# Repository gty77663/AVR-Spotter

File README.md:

# AVR Spotter
  
[Credit for logo inspiration](https://commons.m.wikimedia.org/wiki/File:Spark_By_Alexander_Skowalsky_756341.svg)

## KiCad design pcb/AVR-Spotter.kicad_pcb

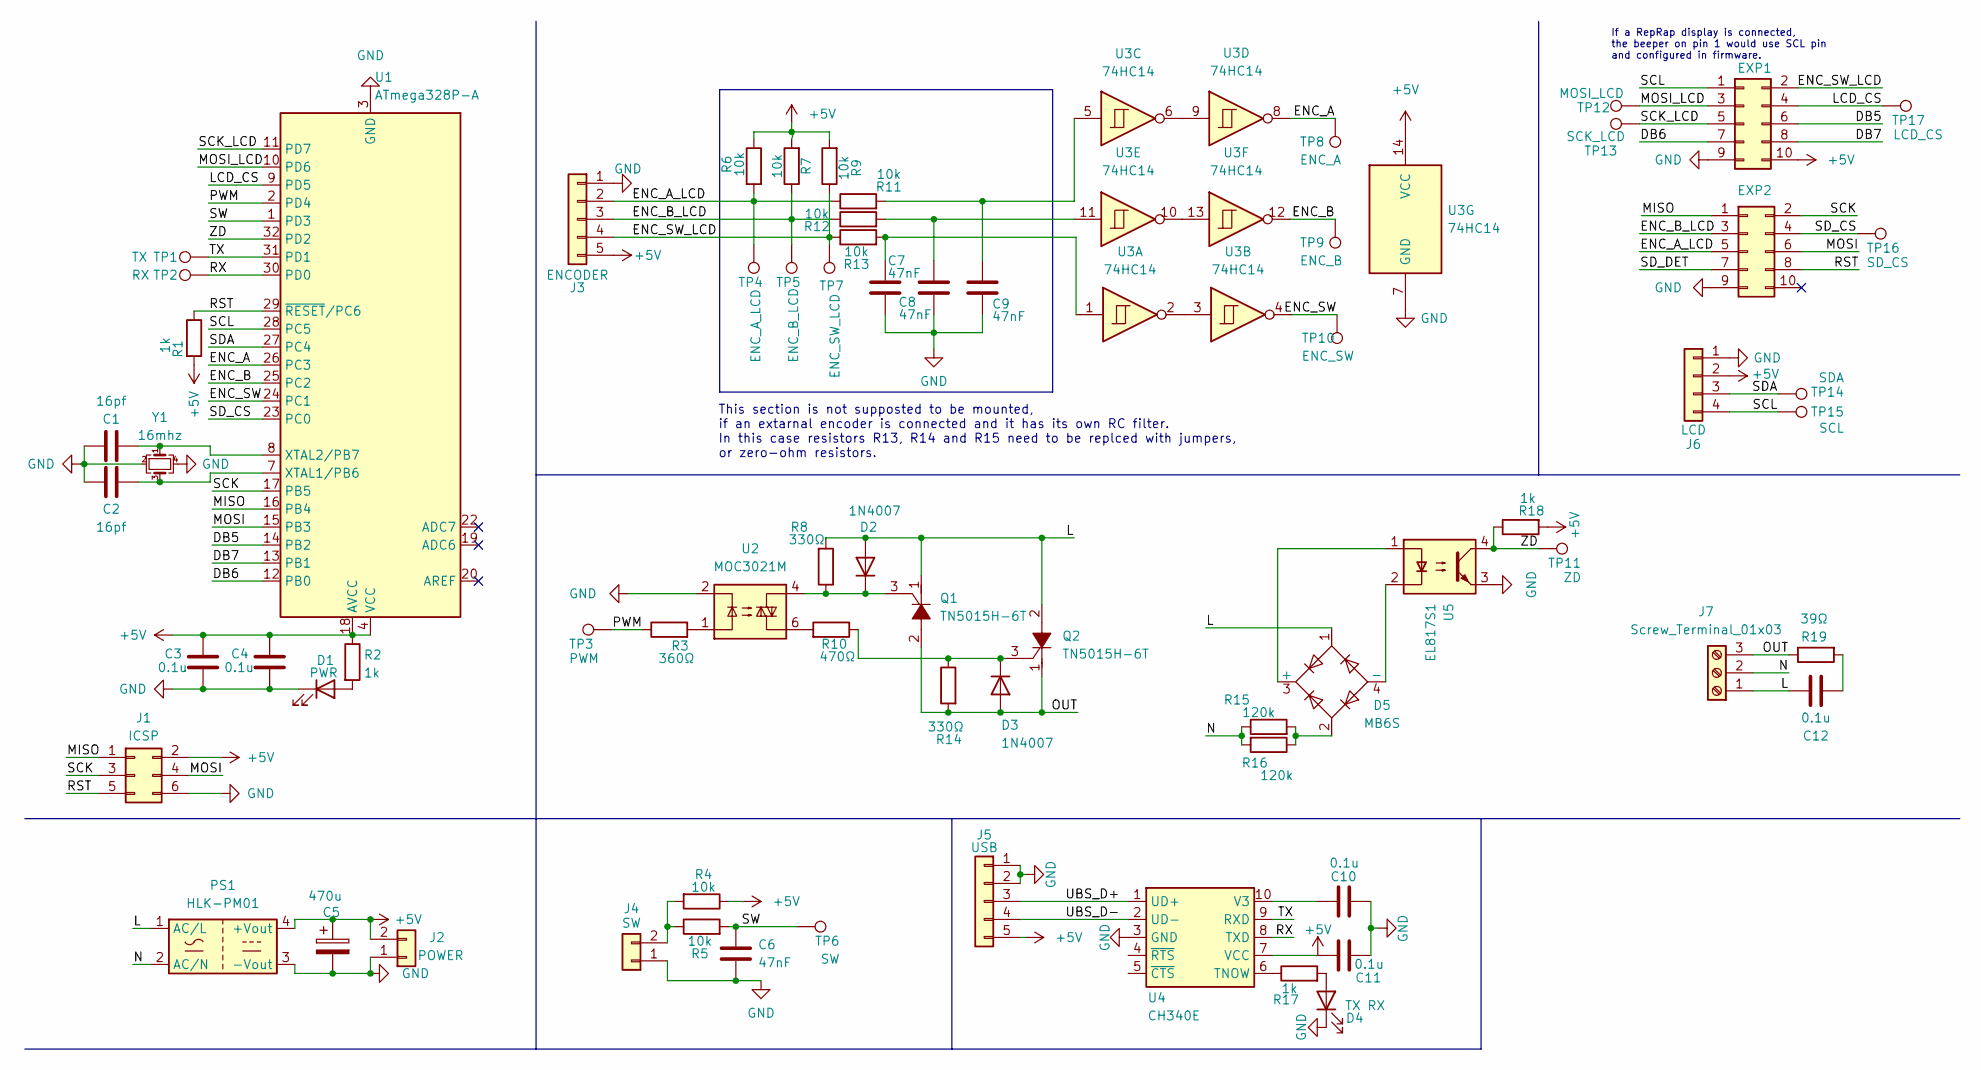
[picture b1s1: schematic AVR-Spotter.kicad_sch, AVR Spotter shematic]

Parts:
C1, C2: 16pf; C_0402_1005Metric
C3, C4, C10, C11: 0.1u; C_0402_1005Metric
C5: 470u; CP_Radial_D6.3mm_P2.50mm
C6, C7, C8, C9: 47nF; C_0402_1005Metric
C12: 0.1u; C_1206_3216Metric
D1: PWR; LED_0603_1608Metric
D2: 1N4007; D_SMA
D3: 1N4007; D_SMA; LCSC Part C727081
D4: TX RX; LED_0603_1608Metric
D5: MB6S; TO-269AA
EXP1, EXP2: Header_2x05_P2.54mm_Vertical; IDC-Header_2x05_P2.54mm_Vertical
J1: ICSP; PinHeader_2x03_P2.54mm_Vertical
J2: POWER; JST_XH_B2B-XH-A_1x02_P2.50mm_Vertical
J3: ENCODER; JST_XH_B5B-XH-A_1x05_P2.50mm_Vertical
J4: SW; JST_XH_B2B-XH-A_1x02_P2.50mm_Vertical
J5: USB; PinHeader_1x05_P2.54mm_Vertical
J6: LCD; JST_XH_B4B-XH-A_1x04_P2.50mm_Vertical
J7: Screw_Terminal_01x03; PhoenixContact_GMSTBA_2,5_3-G-7,62_1x03_P7.62mm_Horizontal
PS1: HLK-PM01; Converter_ACDC_HiLink_HLK-PMxx
Q1, Q2: TN5015H-6T; TO-220-3; MPN TN5015H-6T; Digi-Key_PN 497-17607-ND
R1, R2, R17, R18: 1k; R_0402_1005Metric
R3: 360Ω; R_0402_1005Metric
R4, R5, R6, R7, R9, R11, R12, R13: 10k; R_0402_1005Metric
R8, R14: 330Ω; R_1206_3216Metric_Pad1.30x1.75mm_HandSolder; LCSC Part C25374
R10: 470Ω; R_1210_3225Metric_Pad1.30x2.65mm_HandSolder; LCSC Part C473642
R15, R16: 120k; R_1210_3225Metric_Pad1.30x2.65mm_HandSolder
R19: 39Ω; R_1210_3225Metric
TP1: TX; TestPoint_Pad_D1.0mm
TP2: RX; TestPoint_Pad_D1.0mm
TP3: PWM; TestPoint_Pad_D1.0mm
TP4: ENC_A_LCD; TestPoint_Pad_D1.0mm
TP5: ENC_B_LCD; TestPoint_Pad_D1.0mm
TP6: SW; TestPoint_Pad_D1.0mm
TP7: ENC_SW_LCD; TestPoint_Pad_D1.0mm
TP8: ENC_A; TestPoint_Pad_D1.0mm
TP9: ENC_B; TestPoint_Pad_D1.0mm
TP10: ENC_SW; TestPoint_Pad_D1.0mm
TP11: ZD; TestPoint_Pad_D1.0mm
TP12: MOSI_LCD; TestPoint_Pad_D1.0mm
TP13: SCK_LCD; TestPoint_Pad_D1.0mm
TP14: SDA; TestPoint_Pad_D1.0mm
TP15: SCL; TestPoint_Pad_D1.0mm
TP16: SD_CS; TestPoint_Pad_D1.0mm
TP17: LCD_CS; TestPoint_Pad_D1.0mm
U1: ATmega328P-A; TQFP-32_7x7mm_P0.8mm
U2: MOC3021M; SMDIP-6_W9.53mm
U3: 74HC14; SO-14_3.9x8.65mm_P1.27mm
U4: CH340E; MSOP-10_3x3mm_P0.5mm
U5: EL817S1; SMD-4_4.6x6.5mm_P2.54mm
Y1: 16mhz; Crystal_SMD_3225-4Pin_3.2x2.5mm

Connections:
+5V: C3.1, C4.1, C5.1, EXP1.10, J1.2, J2.2, J3.5, J5.5, J6.2, PS1.4 (+Vout), R1.2, R2.1, R4.1, R6.1, R7.2, R9.2, R18.2, U1.4 (VCC), U1.6 (VCC), U1.18 (AVCC), U3.14 (VCC)
/DB5: EXP1.6, U1.14 (PB2)
/DB6: EXP1.7, U1.12 (PB0)
/DB7: EXP1.8, U1.13 (PB1)
/ENC_A: TP8.1, U1.26 (PC3), U3.8
/ENC_A_LCD: EXP2.5, J3.2, R6.2, R11.1, TP4.1
/ENC_B: TP9.1, U1.25 (PC2), U3.12
/ENC_B_LCD: EXP2.3, J3.3, R7.1, R12.1, TP5.1
/ENC_SW: TP10.1, U1.24 (PC1), U3.4
/ENC_SW_LCD: EXP1.2, J3.4, R9.1, R13.1, TP7.1
/L: C12.2, D2.2 (A), D5.1, J7.1, PS1.1 (AC/L), Q1.1 (C), Q2.2 (A), R8.2
/LCD_CS: EXP1.4, TP17.1, U1.9 (PD5)
/MISO: EXP2.1, J1.1, U1.16 (PB4)
/MOSI: EXP2.6, J1.4, U1.15 (PB3)
/MOSI_LCD: EXP1.3, TP12.1, U1.10 (PD6)
/N: J7.2, PS1.2 (AC/N), R15.1, R16.2
/OUT: D3.2 (A), J7.3, Q1.2 (A), Q2.1 (C), R14.2, R19.1
/PWM: R3.1, TP3.1, U1.2 (PD4)
/RST: EXP2.8, J1.5, R1.1, U1.29 (~RESET/PC6)
/RX: TP2.1, U1.30 (PD0), U4.8 (TXD)
/SCK: EXP2.2, J1.3, U1.17 (PB5)
/SCK_LCD: EXP1.5, TP13.1, U1.11 (PD7)
/SCL: EXP1.1, J6.4, TP15.1, U1.28 (PC5)
/SDA: J6.3, TP14.1, U1.27 (PC4)
/SD_CS: EXP2.4, TP16.1, U1.23 (PC0)
/SD_DET: EXP2.7
/SW: C6.1, R5.2, TP6.1, U1.1 (PD3)
/TX: TP1.1, U1.31 (PD1), U4.9 (RXD)
/UBS_D+: J5.3, U4.1 (UD+)
/UBS_D-: J5.4, U4.2 (UD-)
/ZD: R18.1, TP11.1, U1.32 (PD2), U5.4
GND: C1.2, C2.1, C3.2, C4.2, C5.2, C6.2, C7.2, C8.2, C9.2, C10.1, C11.1, D1.1 (K), D4.1 (K), EXP1.9, EXP2.9, J1.6, J2.1, J3.1, J4.1, J5.1, J5.2, J6.1, PS1.3 (-Vout), U1.3 (GND), U1.5 (GND), U1.21 (GND), U2.2, U3.7 (GND), U4.3 (GND), U5.3, Y1.2, Y1.4
unnamed: C1.1, U1.8 (XTAL2/PB7), Y1.1
unnamed: C2.2, U1.7 (XTAL1/PB6), Y1.3
unnamed: C7.1, R13.2, U3.1
unnamed: C8.1, R12.2, U3.11
unnamed: C9.1, R11.2, U3.5
unnamed: C10.2, U4.10 (V3)
unnamed: C11.2, U4.7 (VCC)
unnamed: C12.1, R19.2
unnamed: D1.2 (A), R2.2
unnamed: D2.1 (K), Q1.3 (G), R8.1, U2.4
unnamed: D3.1 (K), Q2.3 (G), R10.1, R14.1
unnamed: D4.2 (A), R17.2
unnamed: D5.2, R15.2, R16.1
unnamed: D5.3 (+), U5.1
unnamed: D5.4 (-), U5.2
unnamed: J4.2, R4.2, R5.1
unnamed: R3.2, U2.1
unnamed: R10.2, U2.6
unnamed: R17.1, U4.6 (TNOW)
unnamed: U3.2, U3.3
unnamed: U3.6, U3.9
unnamed: U3.10, U3.13

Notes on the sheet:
This section is not supposted to be mounted, if an extarnal encoder is connected and it has its own RC filter. In this case resistors R13, R14 and R15 need to be replced with jumpers, or zero-ohm resistors.
If a RepRap display is connected, the beeper on pin 1 would use SCL pin and configured in firmware.

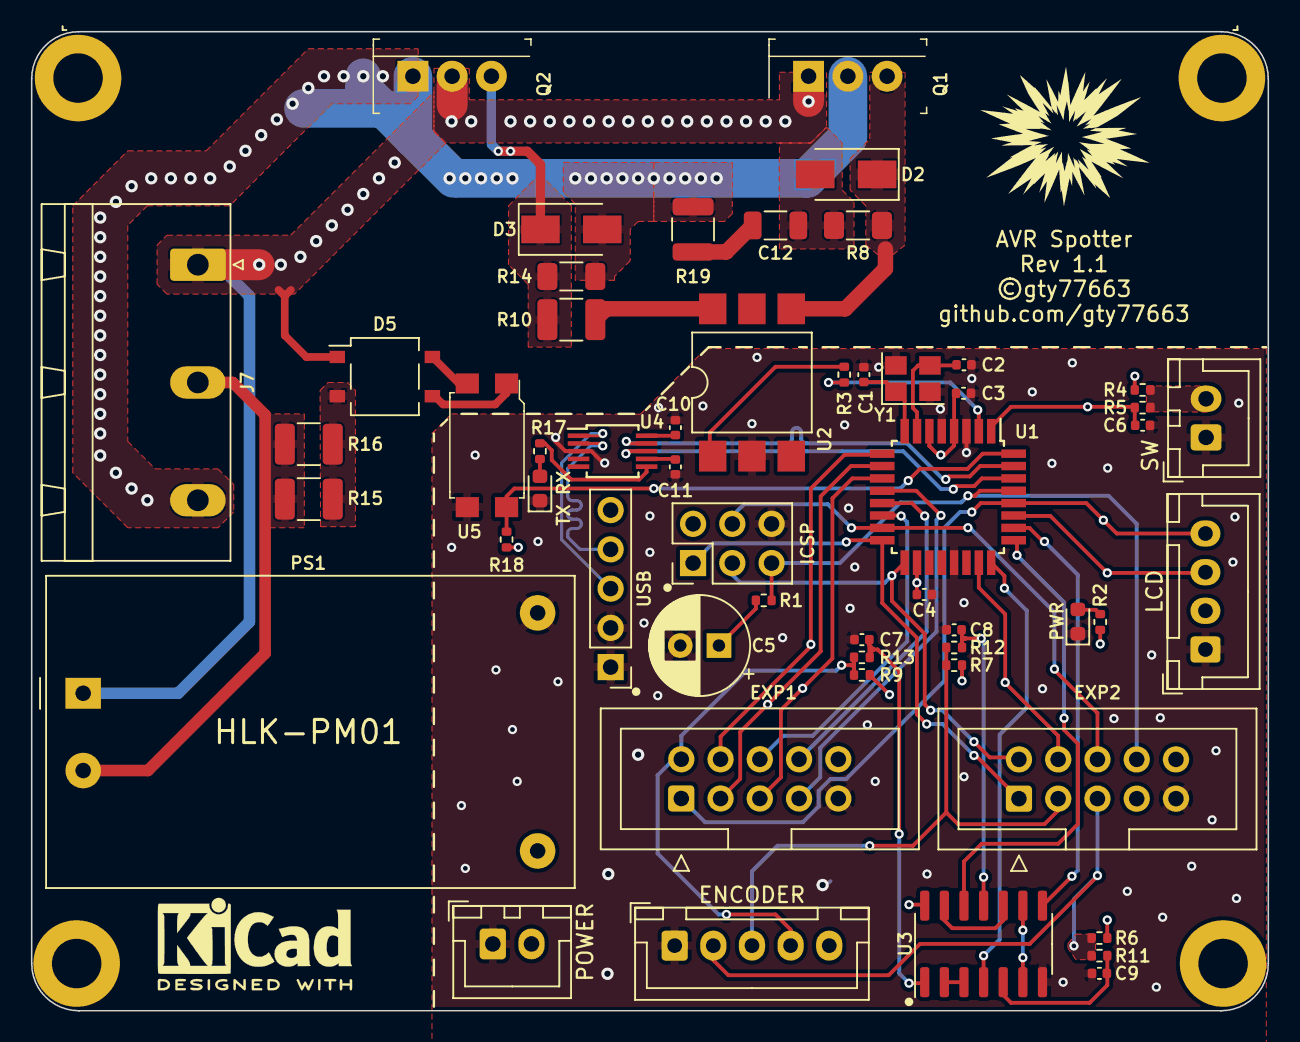
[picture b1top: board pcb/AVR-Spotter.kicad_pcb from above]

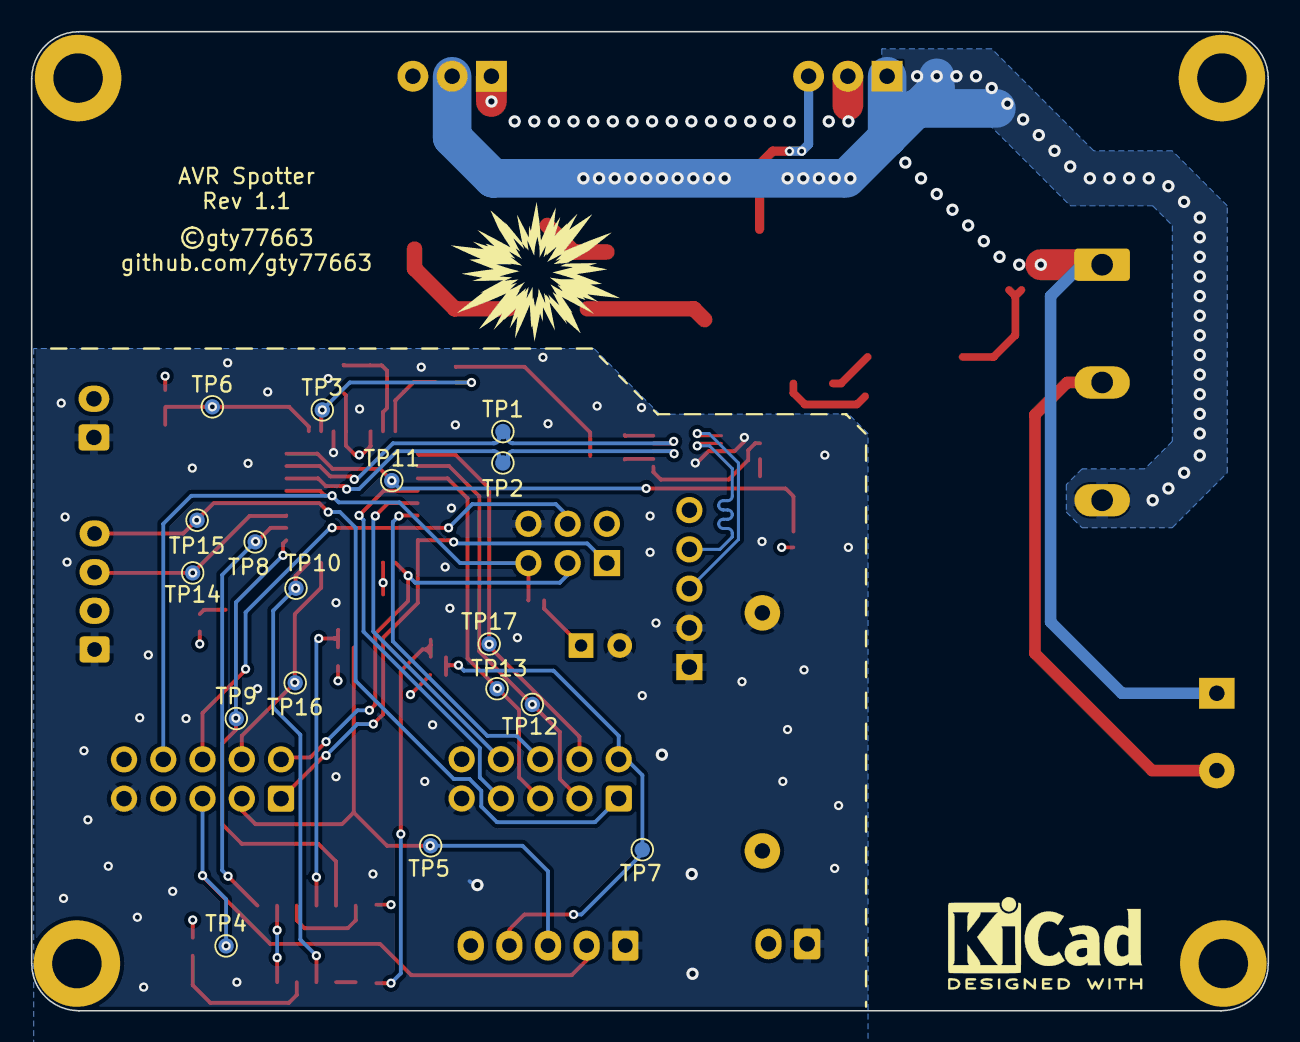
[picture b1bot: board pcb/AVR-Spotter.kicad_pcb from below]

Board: 4 copper layers, 80.0 x 63.3 mm, 76 parts (17 on the bottom side), 53 nets.

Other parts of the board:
HS: Heatsink_76x45x21mm_2Holes
TH1, TH2, TH3, TH4: MountingHole_3.2mm_M3_DIN965_Pad

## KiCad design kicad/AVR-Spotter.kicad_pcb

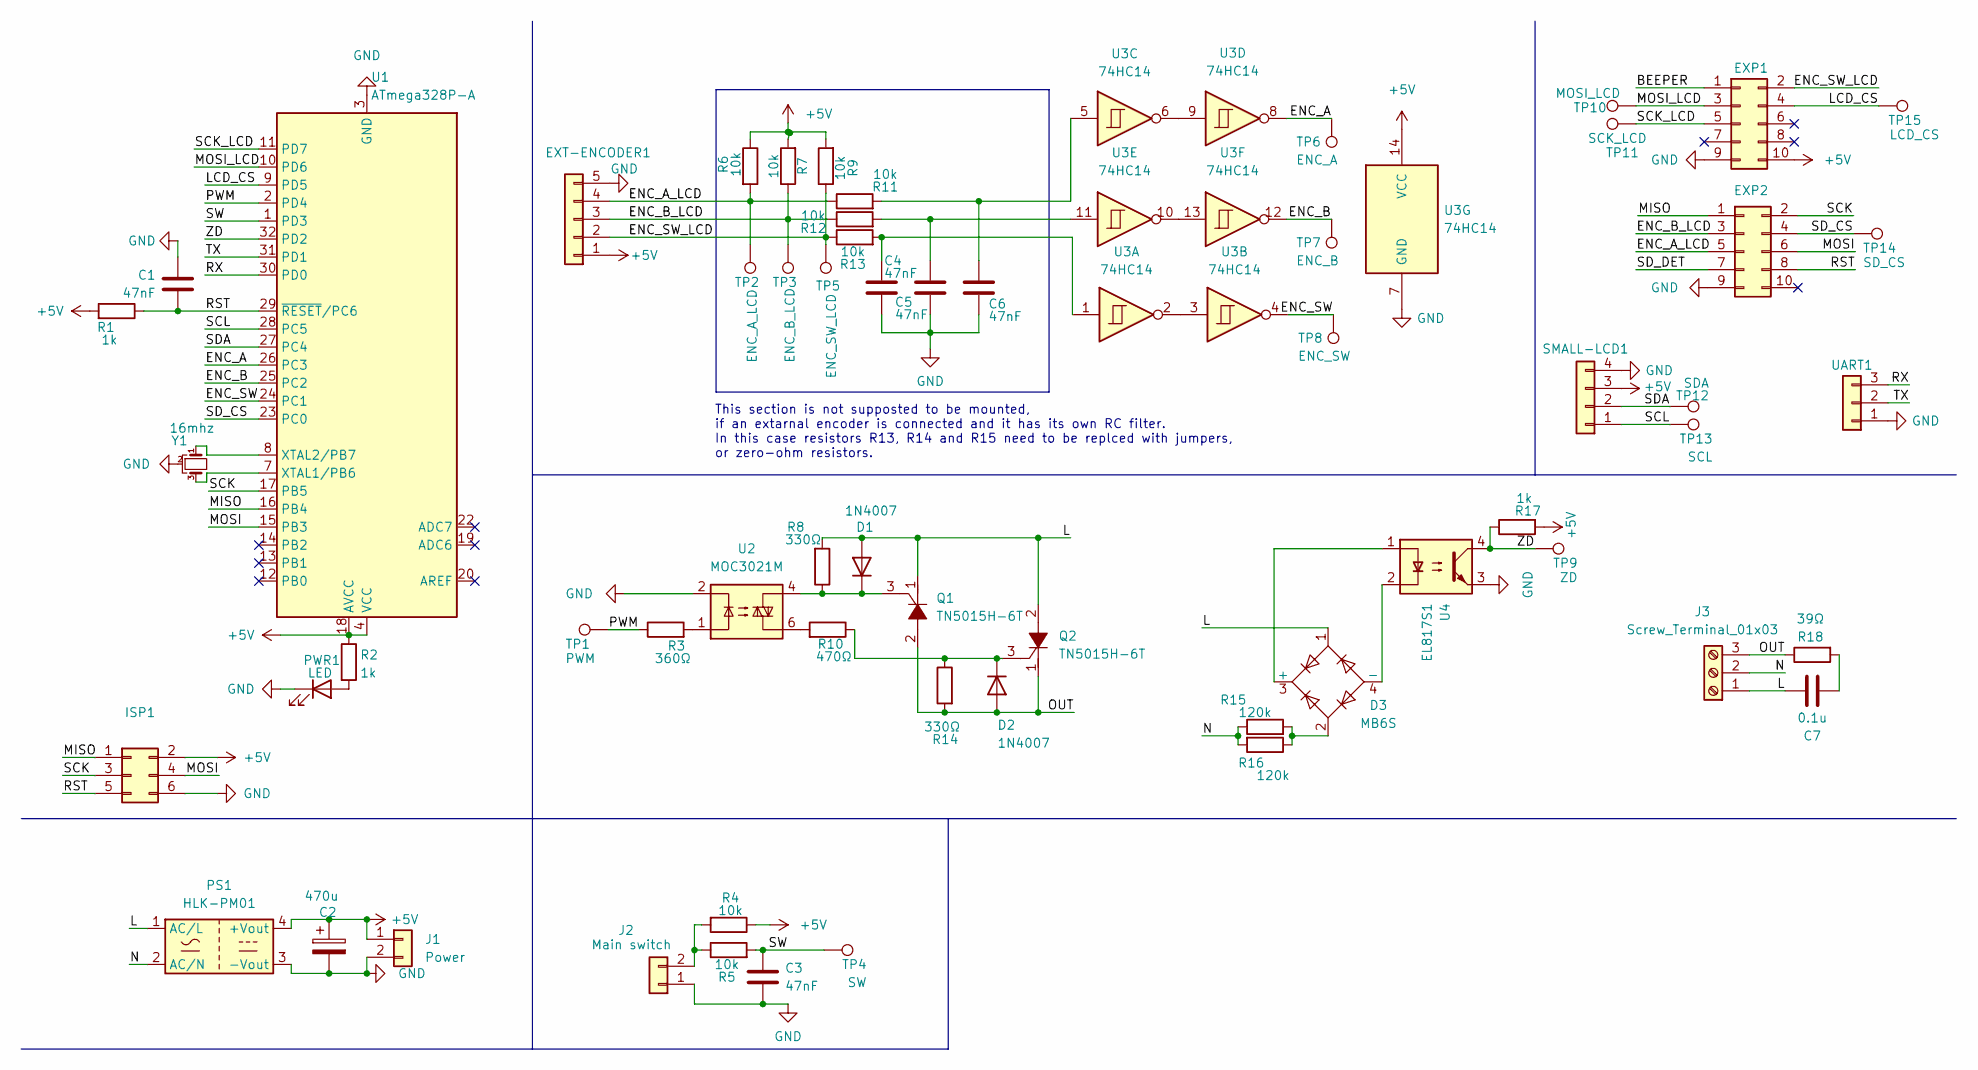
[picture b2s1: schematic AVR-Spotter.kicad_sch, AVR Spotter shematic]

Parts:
C1, C3, C4, C5, C6: 47nF; C_0603_1608Metric
C2: 470u; CP_Radial_D6.3mm_P2.50mm
C7: 0.1u; C_1206_3216Metric
D1: 1N4007; D_SMA
D2: 1N4007; D_SMA; LCSC Part C727081
D3: MB6S; TO-269AA
EXP1: EXP1; IDC-Header_2x05_P2.54mm_Vertical
EXP2: EXP2; IDC-Header_2x05_P2.54mm_Vertical
EXT-ENCODER1: Conn_01x05; JST_XH_B5B-XH-A_1x05_P2.50mm_Vertical
ISP1: ISP; PinHeader_2x03_P2.54mm_Vertical
J1: Power; JST_XH_B2B-XH-A_1x02_P2.50mm_Vertical
J2: Main switch; JST_XH_B2B-XH-A_1x02_P2.50mm_Vertical
J3: Screw_Terminal_01x03; PhoenixContact_GMSTBA_2,5_3-G-7,62_1x03_P7.62mm_Horizontal
PS1: HLK-PM01; Converter_ACDC_HiLink_HLK-PMxx
PWR1: LED; LED_0603_1608Metric
Q1, Q2: TN5015H-6T; TO-220-3; MPN TN5015H-6T; Digi-Key_PN 497-17607-ND
R1, R2, R17: 1k; R_0603_1608Metric_Pad0.98x0.95mm_HandSolder
R3: 360Ω; R_0603_1608Metric_Pad0.98x0.95mm_HandSolder
R4, R5, R6, R7, R9, R11, R12, R13: 10k; R_0603_1608Metric
R8, R14: 330Ω; R_1206_3216Metric_Pad1.30x1.75mm_HandSolder; LCSC Part C25374
R10: 470Ω; R_1210_3225Metric_Pad1.30x2.65mm_HandSolder; LCSC Part C473642
R15, R16: 120k; R_1210_3225Metric_Pad1.30x2.65mm_HandSolder
R18: 39Ω; R_1210_3225Metric
SMALL-LCD1: LCD; JST_XH_B4B-XH-A_1x04_P2.50mm_Vertical
TP1: PWM; TestPoint_Pad_D1.0mm
TP2: ENC_A_LCD; TestPoint_Pad_D1.0mm
TP3: ENC_B_LCD; TestPoint_Pad_D1.0mm
TP4: SW; TestPoint_Pad_D1.0mm
TP5: ENC_SW_LCD; TestPoint_Pad_D1.0mm
TP6: ENC_A; TestPoint_Pad_D1.0mm
TP7: ENC_B; TestPoint_Pad_D1.0mm
TP8: ENC_SW; TestPoint_Pad_D1.0mm
TP9: ZD; TestPoint_Pad_D1.0mm
TP10: MOSI_LCD; TestPoint_Pad_D1.0mm
TP11: SCK_LCD; TestPoint_Pad_D1.0mm
TP12: SDA; TestPoint_Pad_D1.0mm
TP13: SCL; TestPoint_Pad_D1.0mm
TP14: SD_CS; TestPoint_Pad_D1.0mm
TP15: LCD_CS; TestPoint_Pad_D1.0mm
U1: ATmega328P-A; TQFP-32_7x7mm_P0.8mm
U2: MOC3021M; SMDIP-6_W9.53mm
U3: 74HC14; SO-14_3.9x8.65mm_P1.27mm
U4: EL817S1; SMD-4_4.6x6.5mm_P2.54mm
UART1: Conn_01x03; PinHeader_1x03_P2.54mm_Vertical
Y1: 16mhz; Resonator_SMD_Murata_CSTxExxV-3Pin_3.0x1.1mm

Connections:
+5V: C2.1, EXP1.10, EXT-ENCODER1.1, ISP1.2, J1.1, PS1.4 (+Vout), R1.2, R2.1, R4.1, R6.1, R7.2, R9.2, R17.2, SMALL-LCD1.3, U1.4 (VCC), U1.6 (VCC), U1.18 (AVCC), U3.14 (VCC)
/BEEPER: EXP1.1
/ENC_A: TP6.1, U1.26 (PC3), U3.8
/ENC_A_LCD: EXP2.5, EXT-ENCODER1.4, R6.2, R11.1, TP2.1
/ENC_B: TP7.1, U1.25 (PC2), U3.12
/ENC_B_LCD: EXP2.3, EXT-ENCODER1.3, R7.1, R12.1, TP3.1
/ENC_SW: TP8.1, U1.24 (PC1), U3.4
/ENC_SW_LCD: EXP1.2, EXT-ENCODER1.2, R9.1, R13.1, TP5.1
/L: C7.2, D1.2 (A), D3.1, J3.1, PS1.1 (AC/L), Q1.1 (C), Q2.2 (A), R8.2
/LCD_CS: EXP1.4, TP15.1, U1.9 (PD5)
/MISO: EXP2.1, ISP1.1, U1.16 (PB4)
/MOSI: EXP2.6, ISP1.4, U1.15 (PB3)
/MOSI_LCD: EXP1.3, TP10.1, U1.10 (PD6)
/N: J3.2, PS1.2 (AC/N), R15.1, R16.2
/OUT: D2.2 (A), J3.3, Q1.2 (A), Q2.1 (C), R14.2, R18.1
/PWM: R3.1, TP1.1, U1.2 (PD4)
/RST: C1.1, EXP2.8, ISP1.5, R1.1, U1.29 (~RESET/PC6)
/RX: U1.30 (PD0), UART1.3
/SCK: EXP2.2, ISP1.3, U1.17 (PB5)
/SCK_LCD: EXP1.5, TP11.1, U1.11 (PD7)
/SCL: SMALL-LCD1.1, TP13.1, U1.28 (PC5)
/SDA: SMALL-LCD1.2, TP12.1, U1.27 (PC4)
/SD_CS: EXP2.4, TP14.1, U1.23 (PC0)
/SD_DET: EXP2.7
/SW: C3.1, R5.2, TP4.1, U1.1 (PD3)
/TX: U1.31 (PD1), UART1.2
/ZD: R17.1, TP9.1, U1.32 (PD2), U4.4
GND: C1.2, C2.2, C3.2, C4.2, C5.2, C6.2, EXP1.9, EXP2.9, EXT-ENCODER1.5, ISP1.6, J1.2, J2.1, PS1.3 (-Vout), PWR1.1 (K), SMALL-LCD1.4, U1.3 (GND), U1.5 (GND), U1.21 (GND), U2.2, U3.7 (GND), U4.3, UART1.1, Y1.2
unnamed: C4.1, R13.2, U3.1
unnamed: C5.1, R12.2, U3.11
unnamed: C6.1, R11.2, U3.5
unnamed: C7.1, R18.2
unnamed: D1.1 (K), Q1.3 (G), R8.1, U2.4
unnamed: D2.1 (K), Q2.3 (G), R10.1, R14.1
unnamed: J2.2, R4.2, R5.1
unnamed: PWR1.2 (A), R2.2
unnamed: R3.2, U2.1
unnamed: R10.2, U2.6
unnamed: D3.2, R15.2, R16.1
unnamed: U1.7 (XTAL1/PB6), Y1.3
unnamed: U1.8 (XTAL2/PB7), Y1.1
unnamed: U3.2, U3.3
unnamed: U3.6, U3.9
unnamed: U3.10, U3.13
unnamed: D3.3 (+), U4.1
unnamed: D3.4 (-), U4.2

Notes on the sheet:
This section is not supposted to be mounted, if an extarnal encoder is connected and it has its own RC filter. In this case resistors R13, R14 and R15 need to be replced with jumpers, or zero-ohm resistors.

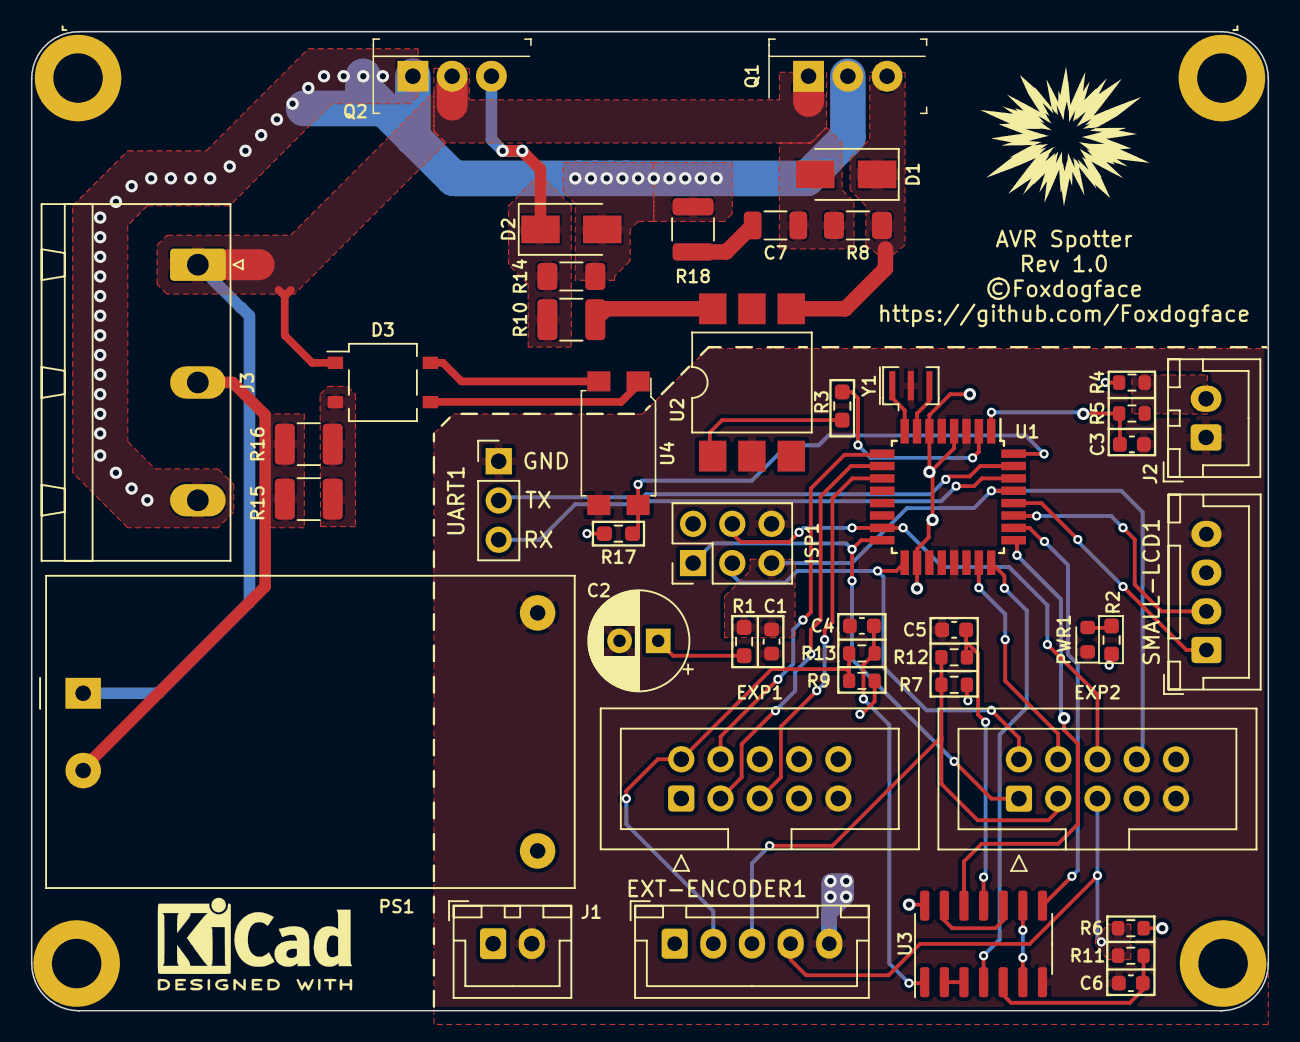
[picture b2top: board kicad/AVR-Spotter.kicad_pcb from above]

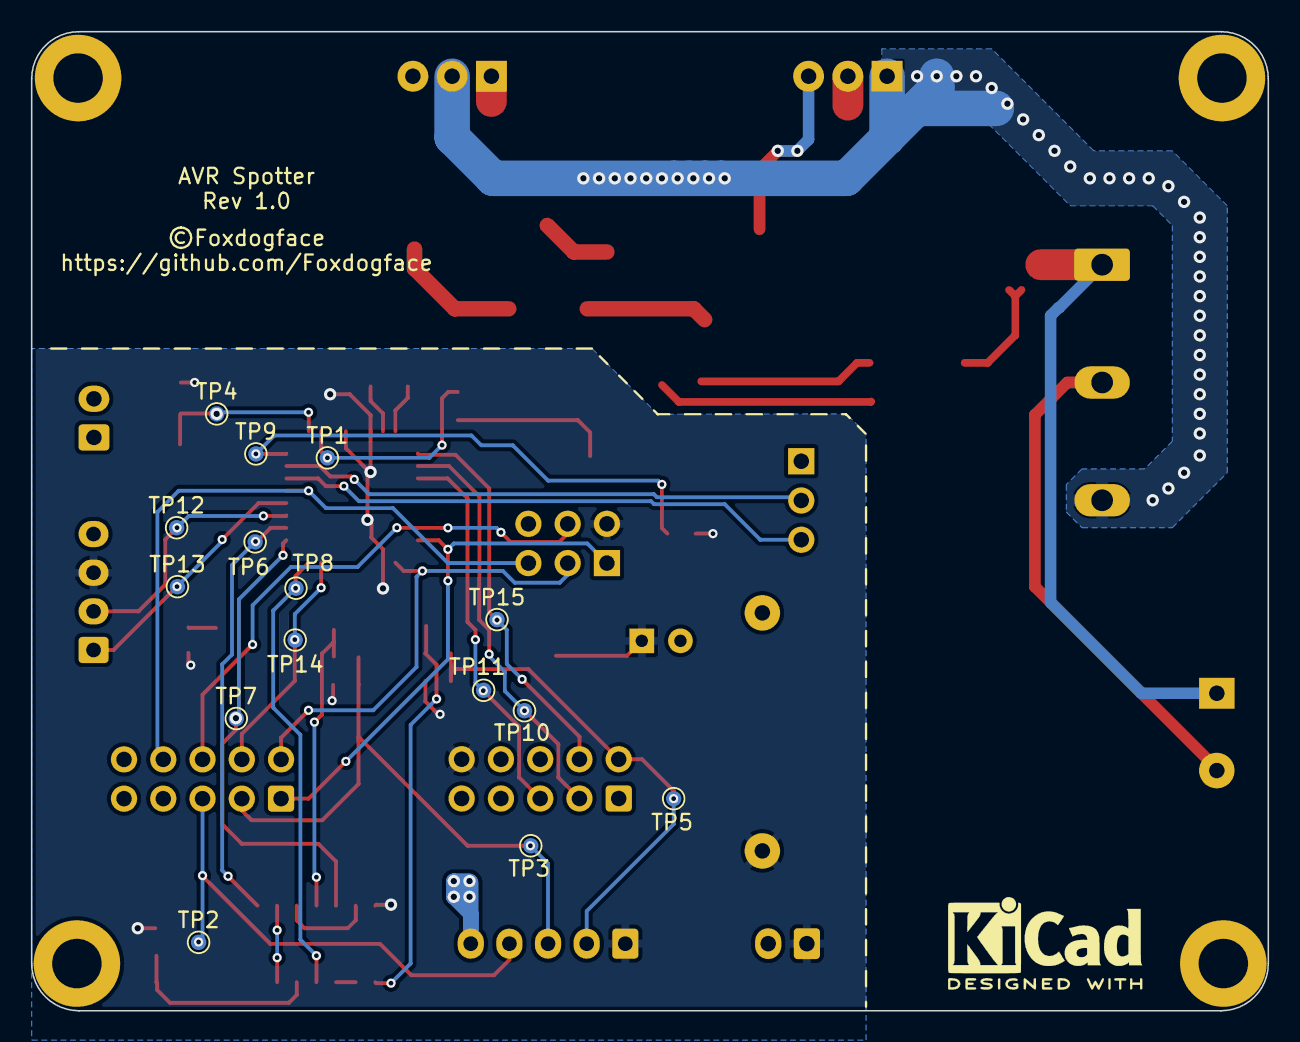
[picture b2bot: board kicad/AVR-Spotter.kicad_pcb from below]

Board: 2 copper layers, 80.0 x 63.3 mm, 62 parts (15 on the bottom side), 44 nets.

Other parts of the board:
HS: Heatsink_76x45x21mm_2Holes

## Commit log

2023-09-19 Update logo
2023-09-19 Again change the logo

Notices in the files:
kicad/AVR-Spotter.kicad_pcb:
©Foxdogface
pcb/AVR-Spotter.kicad_pcb:
©gty77663
